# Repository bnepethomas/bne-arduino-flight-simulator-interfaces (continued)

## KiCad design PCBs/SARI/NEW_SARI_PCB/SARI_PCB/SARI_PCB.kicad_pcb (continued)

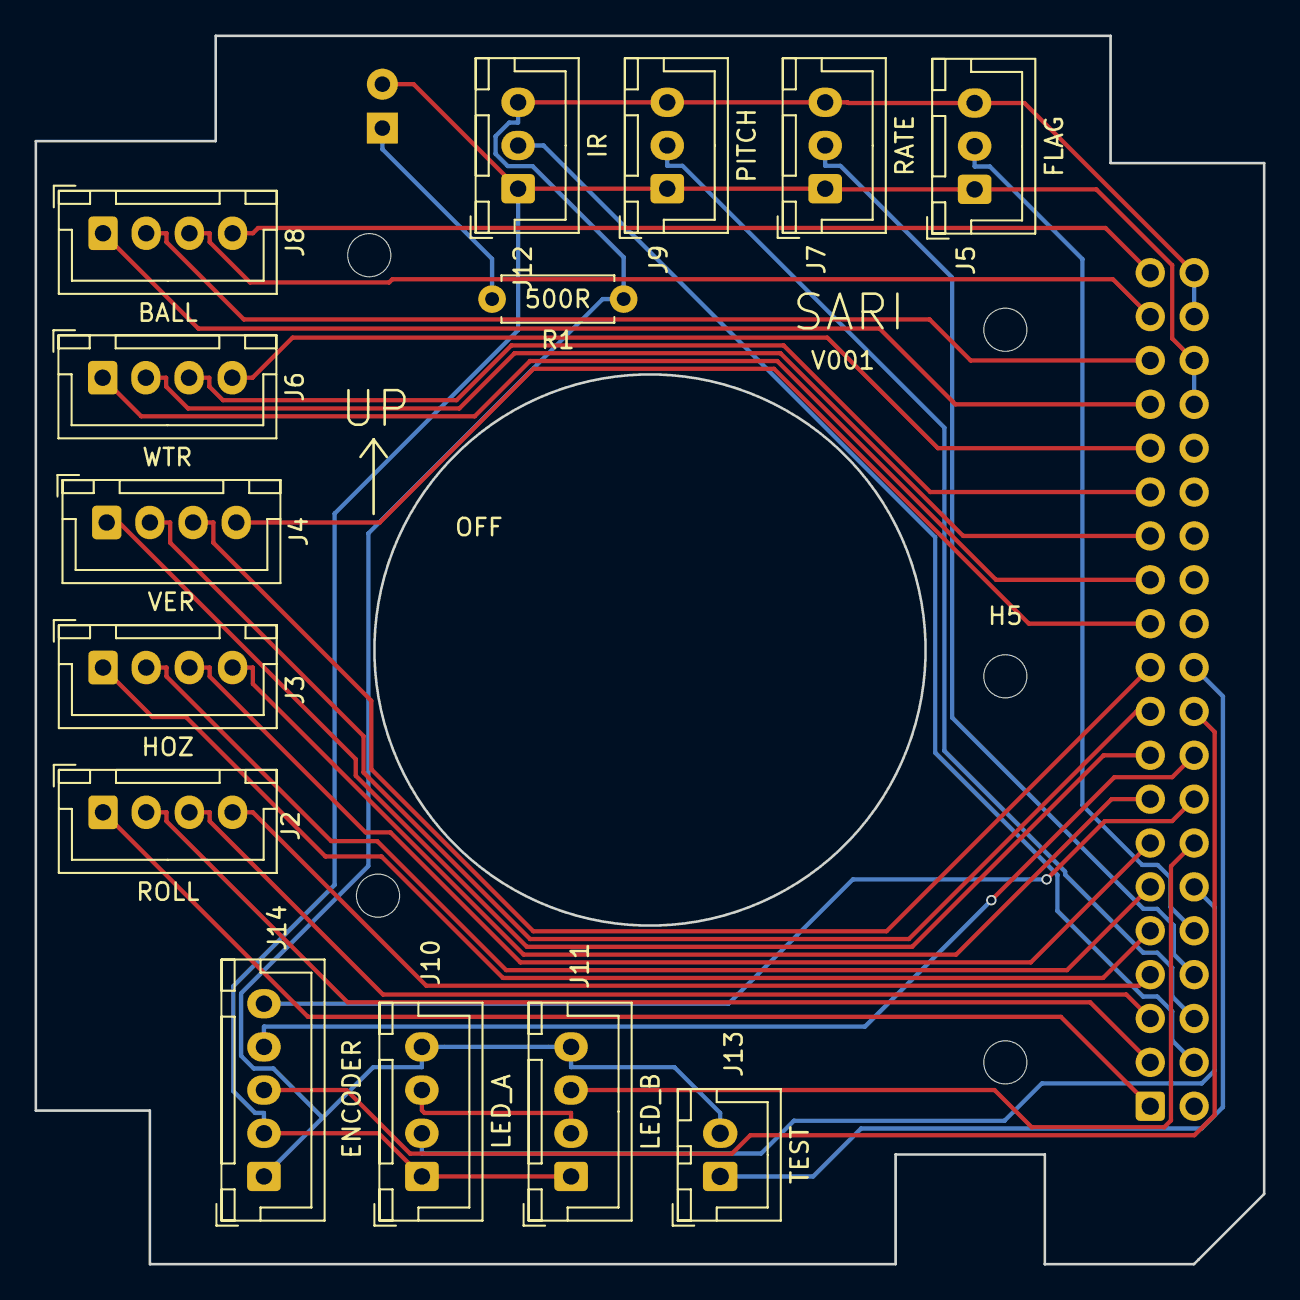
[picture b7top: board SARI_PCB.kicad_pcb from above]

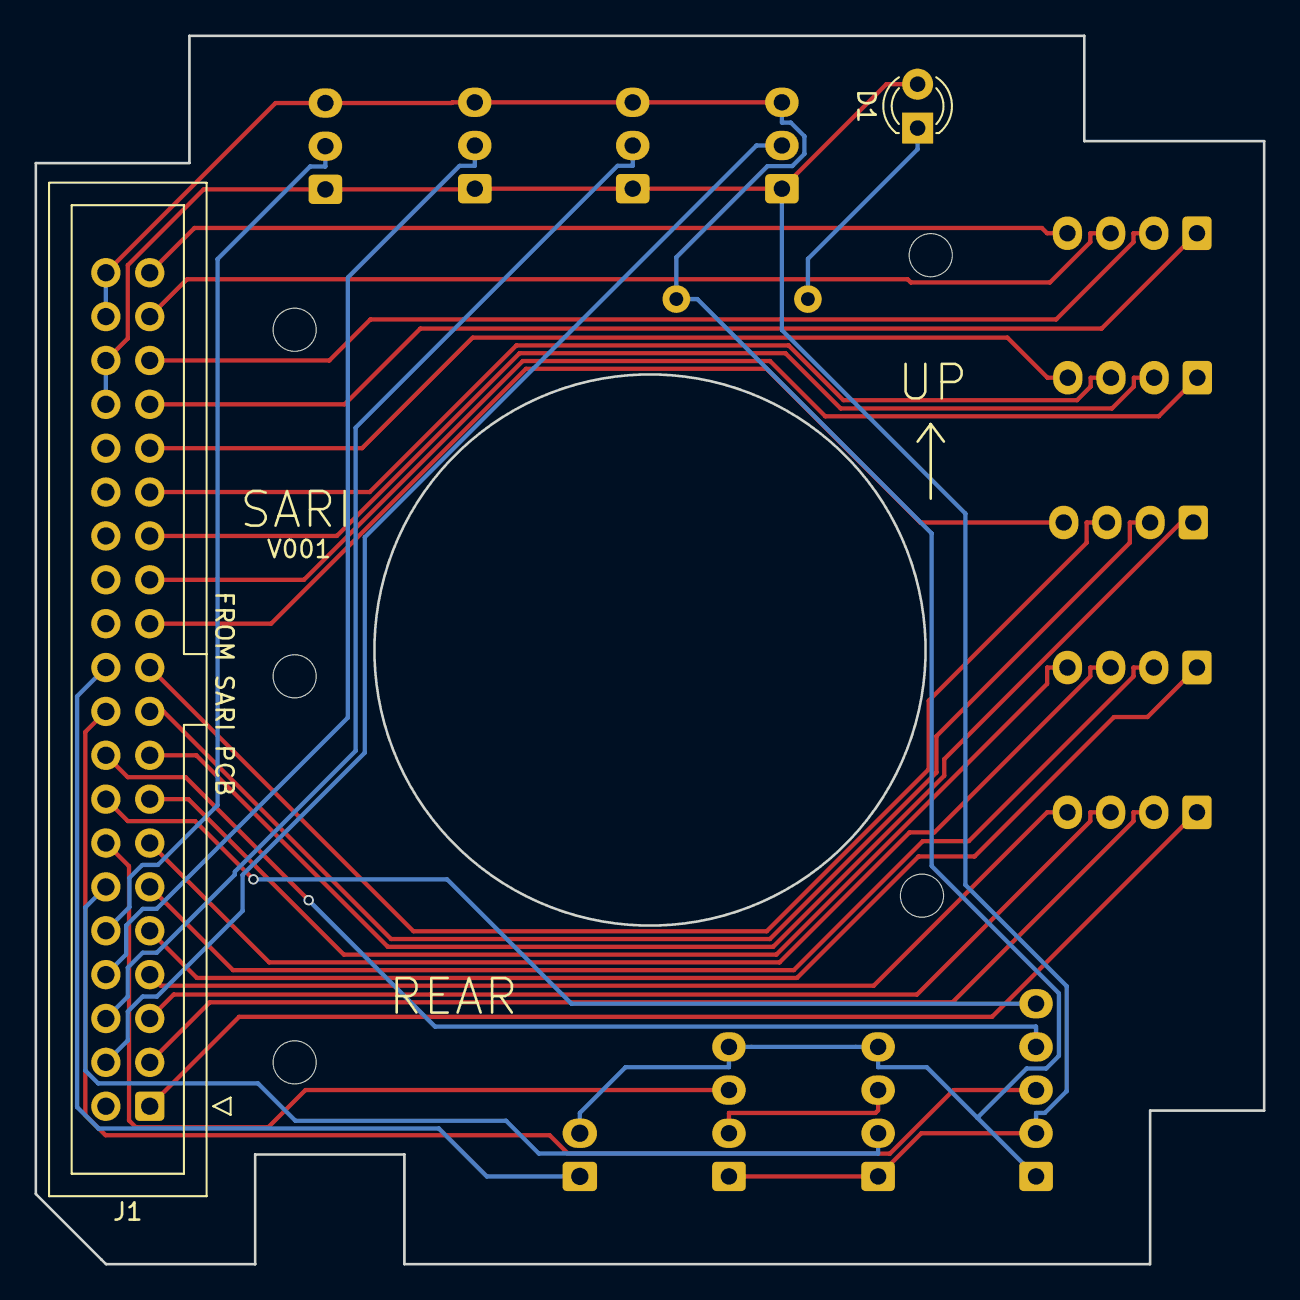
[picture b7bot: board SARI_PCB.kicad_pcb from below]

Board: 2 copper layers, 71.1 x 71.1 mm, 21 parts (2 on the bottom side), 34 nets.

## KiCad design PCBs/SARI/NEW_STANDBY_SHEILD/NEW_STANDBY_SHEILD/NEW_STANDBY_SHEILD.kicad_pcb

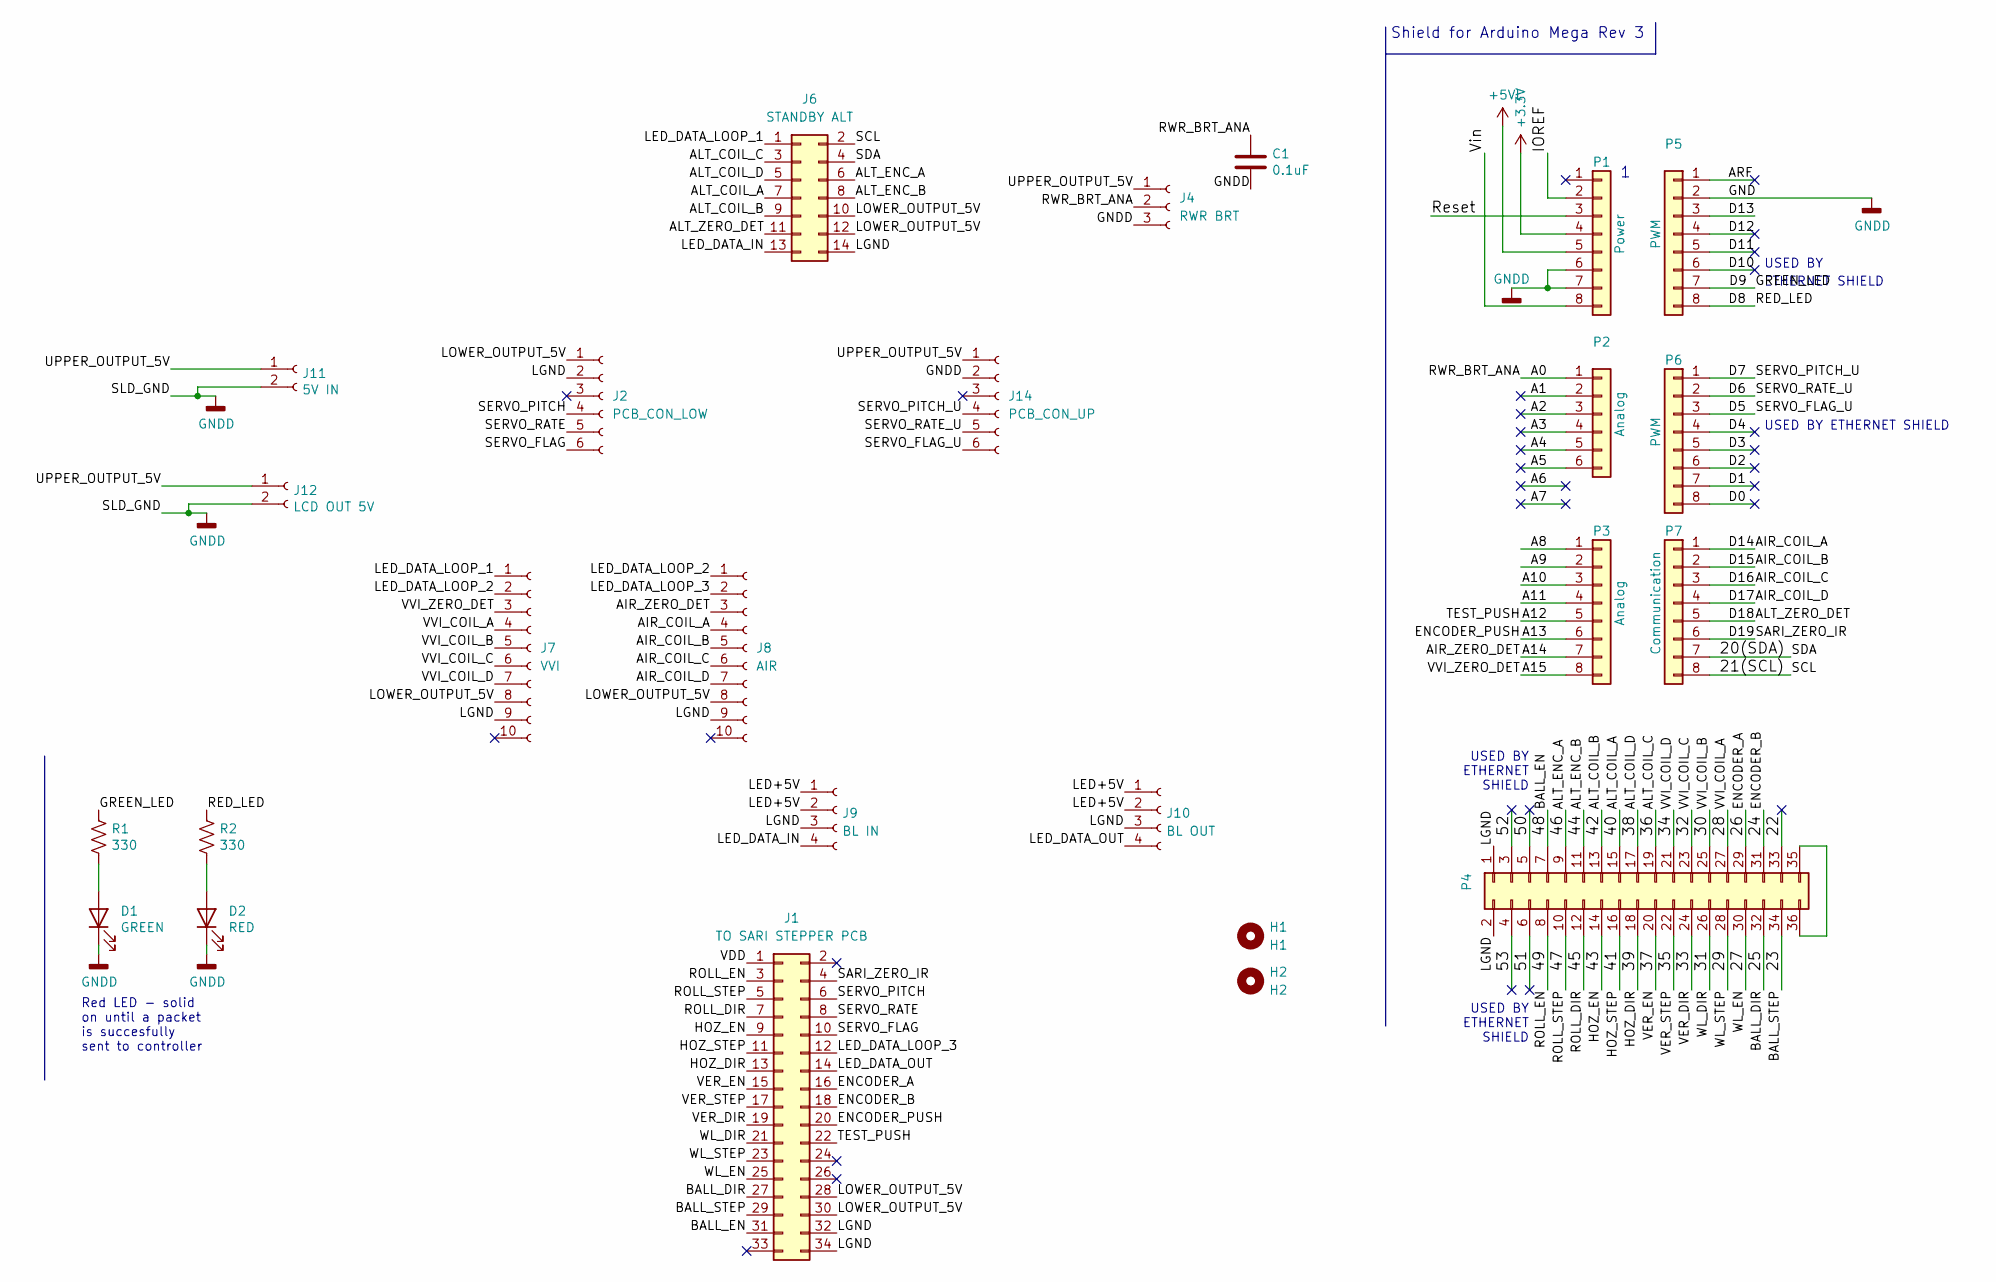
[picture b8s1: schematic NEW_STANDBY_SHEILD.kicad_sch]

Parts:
C1: 0.1uF; C_Disc_D6.0mm_W2.5mm_P5.00mm
D1: GREEN; LED_D3.0mm
D2: RED; LED_D3.0mm
H1: H1; MountingHole_2.5mm
H2: H2; MountingHole_2.5mm
J1: TO SARI STEPPER PCB; IDC-Header_2x17_P2.54mm_Vertical
J2: PCB_CON_LOW; JST_XH_B6B-XH-A_1x06_P2.50mm_Vertical
J4: RWR BRT; JST_XH_B3B-XH-A_1x03_P2.50mm_Vertical
J6: STANDBY ALT; IDC-Header_2x07_P2.54mm_Vertical
J7: VVI; JST_XH_B10B-XH-A_1x10_P2.50mm_Vertical
J8: AIR; JST_XH_B10B-XH-A_1x10_P2.50mm_Vertical
J9: BL IN; Molex_Mini-Fit_Jr_5566-04A_2x02_P4.20mm_Vertical
J10: BL OUT; Molex_Mini-Fit_Jr_5566-04A_2x02_P4.20mm_Vertical
J11: 5V IN; BarrelJack_Horizontal
J12: LCD OUT 5V; BarrelJack_Horizontal
J14: PCB_CON_UP; JST_XH_B6B-XH-A_1x06_P2.50mm_Vertical
P1: Power; Socket_Strip_Arduino_1x08
P2: Analog; Socket_Strip_Arduino_1x06
P3: Analog; Socket_Strip_Arduino_1x08
P4: Digital; Socket_Strip_Arduino_2x18
P5, P6: PWM; Socket_Strip_Arduino_1x08
P7: Communication; Socket_Strip_Arduino_1x08
R1, R2: 330; PT_R_Axial_DIN0204_L3.6mm_D1.6mm_P2.54mm_Vertical

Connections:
+3V3: P1.4
+5VL: P1.5
/21(SCL): J6.2, P7.8
/22: P4.33
/23: J1.29, P4.34
/25: J1.27, P4.32
/27: J1.25, P4.30
/28: J7.4, P4.27
/29: J1.23, P4.28
/30: J7.5, P4.25
/31: J1.21, P4.26
/32: J7.6, P4.23
/33: J1.19, P4.24
/34: J7.7, P4.21
/35: J1.17, P4.22
/37: J1.15, P4.20
/39: J1.13, P4.18
/41: J1.11, P4.16
/43: J1.9, P4.14
/44: J6.8, P4.11
/45: J1.7, P4.12
/46: J6.6, P4.9
/47: J1.5, P4.10
/48: J1.31, P4.7
/49: J1.3, P4.8
/50: P4.5
/51: P4.6
/52: P4.3
/53: P4.4
/A0: C1.1, J4.2, P2.1
/A1: P2.2
/A2: P2.3
/A3: P2.4
/A4: P2.5
/A5: P2.6
/A8: P3.1
/A9: P3.2
/A10: P3.3
/A11: P3.4
/A13: J1.20, P3.6
/A14: J8.3, P3.7
/A15: J7.3, P3.8
/AIR_COIL_A: J8.4, P7.1
/AIR_COIL_B: J8.5, P7.2
/AIR_COIL_C: J8.6, P7.3
/AIR_COIL_D: J8.7, P7.4
/ALT_COIL_A: J6.7, P4.15
/ALT_COIL_B: J6.9, P4.13
/ALT_COIL_C: J6.3, P4.19
/ALT_COIL_D: J6.5, P4.17
/ARF: P5.1
/D0: P6.8
/D1: P6.7
/D2: P6.6
/D3: P6.5
/D4: P6.4
/D5: J14.6, P6.3
/D6: J14.5, P6.2
/D7: J14.4, P6.1
/D8: P5.8, R2.1
/D9: P5.7, R1.1
/D10: P5.6
/D11: P5.5
/D12: P5.4
/D13: P5.3
/D18: J6.11, P7.5
/D19: J1.4, P7.6
/ENCODER_A: J1.16, P4.29
/ENCODER_B: J1.18, P4.31
/IOREF: P1.2
/LED+5V: J9.1, J9.2, J10.1, J10.2
/LED_DATA_IN: J6.13, J9.4
/LED_DATA_LOOP_1: J6.1, J7.1
/LED_DATA_LOOP_2: J7.2, J8.1
/LED_DATA_LOOP_3: J1.12, J8.2
/LED_DATA_OUT: J1.14, J10.4
/LGND: J1.32, J1.34, J2.2, J6.14, J7.9, J8.9, J9.3, J10.3, P4.1, P4.2
/LOWER_OUTPUT_5V: J1.28, J1.30, J2.1, J6.10, J6.12, J7.8, J8.8
/Reset: P1.3
/SDA: J6.4, P7.7
/SERVO_FLAG: J1.10, J2.6
/SERVO_PITCH: J1.6, J2.4
/SERVO_RATE: J1.8, J2.5
/TEST_PUSH: J1.22, P3.5
/UPPER_OUTPUT_5V: J4.1, J11.1, J12.1, J14.1
/VDD: J1.1
/Vin: P1.8
GNDD: C1.2, D1.1 (K), D2.1 (K), J4.3, J11.2, J12.2, J14.2, P1.6, P1.7, P5.2
unnamed: D1.2 (A), R1.2
unnamed: D2.2 (A), R2.2
unnamed: P4.35, P4.36

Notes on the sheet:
Shield for Arduino Mega Rev 3
USED BY ETHERNET SHIELD
ETHERNET SHIELD
USED BY ETHERNET SHIELD
Red LED - solid on until a packet is succesfully sent to controller
USED BY

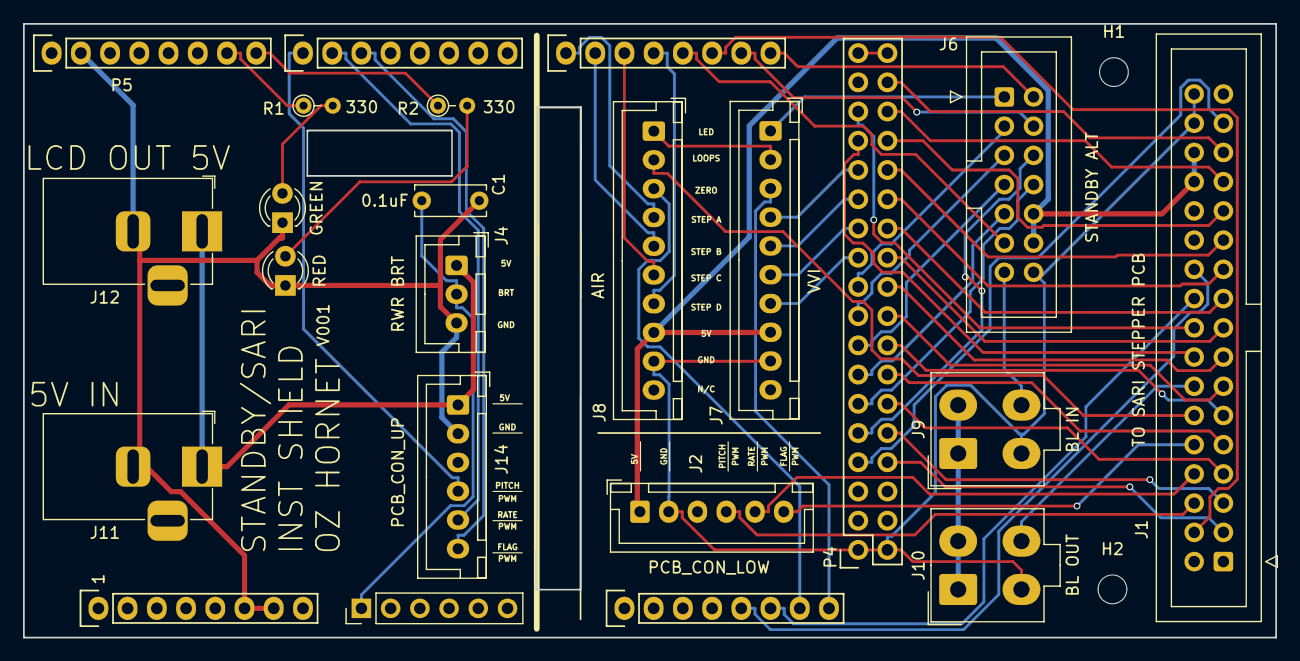
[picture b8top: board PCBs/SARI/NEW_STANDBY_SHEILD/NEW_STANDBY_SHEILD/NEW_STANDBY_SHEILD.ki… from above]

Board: 2 copper layers, 108.8 x 53.3 mm, 25 parts (0 on the bottom side), 61 nets.
